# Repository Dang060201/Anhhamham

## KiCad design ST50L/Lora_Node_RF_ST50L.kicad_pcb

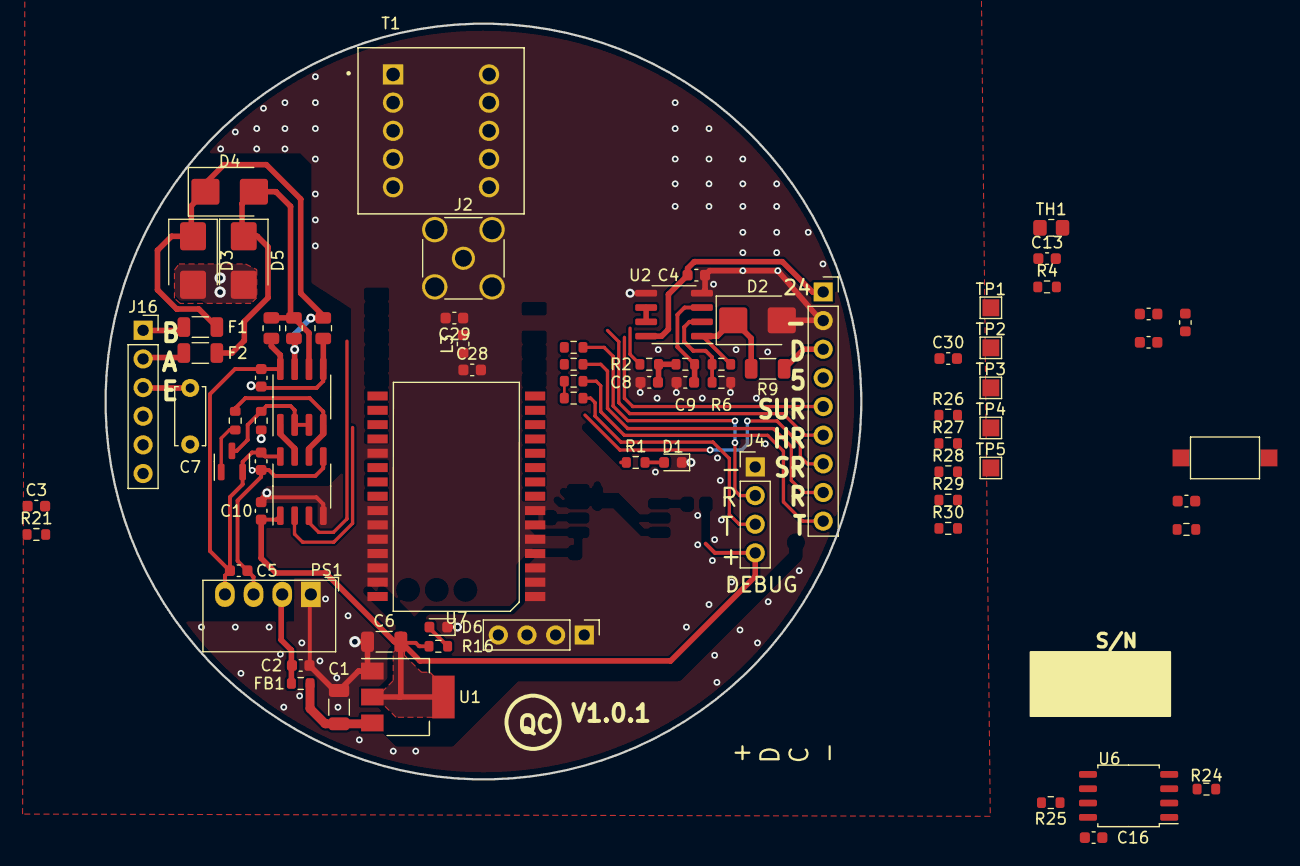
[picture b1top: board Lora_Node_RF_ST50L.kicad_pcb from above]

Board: 2 copper layers, 67.0 x 67.0 mm, 78 parts (0 on the bottom side), 56 nets.

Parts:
C1, C6: 10uF; C_1206_3216Metric
C2, C5: 4.7uF; C_0603_1608Metric
C3, C4, C10, C11, C12, C14, C16: 100nF; C_0603_1608Metric
C7: 4.7nF; C_Disc_D5.0mm_W2.5mm_P5.00mm
C8, C9, C23: 1uF; C_0603_1608Metric
C13: 100n; C_0603_1608Metric
C20: 10uF; C_0603_1608Metric
C28, C29: 7pF; C_0603_1608Metric
C30: 100pF; C_0603_1608Metric
D1, D6: LED; LED_0603_1608Metric
D2: SMBJ12A; D_SMB
D3, D4, D5: SMBJ5.0CA; D_SMB
F1, F2: 0.05A 60V JZ PTC; R_1206_3216Metric
FB1: 100R; R_0603_1608Metric
FB3: FerriteBead; L_0603_1608Metric
J1, J4: Conn_01x04_Pin; PinHeader_1x04_P2.54mm_Vertical
J2: Conn_Coaxial; SMA_Amphenol_132291-12_Vertical
J16: Conn_01x06_Pin; PinSocket_1x06_P2.54mm_Vertical
J17: Conn_01x09_Pin; PinSocket_1x09_P2.54mm_Vertical
L3: 15nH; L_0603_1608Metric
PS1: MEE1S0505SC; Converter_DCDC_Murata_MEE1SxxxxSC_THT
Q1: MMBT3906; SOT-23
R1, R2, R3, R6, R15, R21, R27: 10K; R_0603_1608Metric
R4: 6.8k; R_0603_1608Metric
R5: 33K; R_0603_1608Metric
R7: 6.8K; R_0603_1608Metric
R8: 22K; R_0603_1608Metric
R9: 10R; R_1206_3216Metric
R11, R12, R13: 220R; R_0805_2012Metric
R16: 1K; R_0603_1608Metric
R17, R18, R19, R20: 0R; R_0603_1608Metric
R24, R25: 2.2K; R_0603_1608Metric
R26: 4.7K; R_0603_1608Metric
R28, R29, R30: 22R; R_0603_1608Metric
SW1: SW_Push; SW_SPST_CK_RS282G05A3
T1: EE13; BOBBIN_EE13_6_6
TH1: NTCS0805E3103HLT; R_0805_2012Metric_Pad1.20x1.40mm_HandSolder
TP1, TP4, TP5: digital; TestPoint_Pad_1.5x1.5mm
TP2: 3.3V; TestPoint_Pad_1.5x1.5mm
TP3: GND; TestPoint_Pad_1.5x1.5mm
U1: AMS1117-3.3; SOT-223-3_TabPin2
U2: LM358; SOIC-8_3.9x4.9mm_P1.27mm
U3: CA-IS3722; SOP-8_3.9x4.9mm_P1.27mm
U4: MAX485E; SOIC-8_3.9x4.9mm_P1.27mm
U6: W25Q32JVSS; SOIC-8_5.23x5.23mm_P1.27mm
U7: E77900M22S; E77

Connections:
+3.3V: C6.2, C10.1, C16.1, FB3.2, J1.4, J4.4, R15.1, R16.1, R24.2, R25.2, R26.2, R27.1, TP2.1, U1.2 (VO), U3.1 (VDDA), U6.8 (VCC)
+3.3VP: C14.1, C20.1, FB3.1, U7.28 (VDD)
+5VD: C1.2, FB1.1, J17.4, U1.3 (VI)
+5VP: C5.2, C11.1, C12.1, PS1.4 (+Vout), Q1.2 (E), R13.1, U3.8 (VDDB), U4.8 (VCC)
+24V: C4.1, J17.1, U2.8 (V+)
/A: F2.1, J16.2
/ADC_NTC: C13.1, R4.1, TH1.1, U7.8 (PA1)
/ANT: C28.1, L3.1, U7.14 (ANT)
/A_RS485: D4.2 (A2), D5.1 (A1), F2.2, R12.1, R13.2, U4.6 (A)
/B: F1.1, J16.1
/B_RS485: D3.1 (A1), D4.1 (A1), F1.2, R11.1, R12.2, U4.7 (B)
/DE_RS485: Q1.3 (C), R8.2, U4.2 (~RE), U4.3 (DE)
/DIM10V: J17.3, R9.1
/DS18B20: R26.1, TP1.1, U7.6 (PB8)
/FLASH_CS: U6.1 (~CS), U7.25 (PA15)
/FLASH_HOLD: R25.1, U6.7 (IO3)
/FLASH_MISO: U6.2 (DO(IO1)), U7.2 (PB4)
/FLASH_MOSI: U6.5 (DI(IO0)), U7.3 (PB5)
/FLASH_SCK: U6.6 (CLK), U7.1 (PB3)
/FLASH_WP: R24.1, U6.3 (IO2)
/HLW_RX: J17.8, R19.1
/HLW_TX: J17.9, R20.1
/HRE: R28.2, U7.22 (PB12)
/H_RELAY: J17.6, R28.1
/NRST: C23.1, R15.2, SW1.2, U7.17 (NRST)
/NTC: C3.1, R21.2
/PWM_DAC: R2.1, U7.16 (PA8)
/RUN_LED: R1.1, U7.5 (PB7)
/RX: J4.2, R17.1
/RX_RS485: U3.7 (VI1), U4.1 (RO)
/SRE: R30.2, U7.11 (PA4)
/SURGE: R29.2, U7.23 (PB2)
/SURGE_PULSE: J17.5, R29.1
/SWCLK: J1.3, U7.30 (SWCLK)
/SWDIO: J1.2, U7.29 (SWDIO)
/S_RELAY: J17.7, R30.1
/TX: J4.3, R18.1
/TX_RS485: R7.1, U3.6 (VO2), U4.4 (DI)
/UART1_RX: U3.2 (VO1), U7.21 (PA10)
/UART1_TX: U3.3 (VI2), U7.4 (PB6)
/UART2_RX: R17.2, R19.2, U7.10 (PA3)
/UART2_TX: R18.2, R20.2, U7.9 (PA2)
Earth_Protective: C7.2, J16.3
GND3: C5.1, C7.1, C11.2, C12.2, D3.2 (A2), D5.2 (A2), PS1.3 (-Vout), R8.1, R11.2, U3.5 (GNDB), U4.5 (GND)
GNDPWR: C1.1, C2.1, C3.2, C4.2, C6.1, C8.1, C9.1, C10.2, C13.2, C14.2, C16.2, C20.2, C23.2, C28.2, C29.2, D1.1 (K), D2.2 (A), D6.1 (K), J1.1, J2.2 (Ext), J4.1, J17.2, PS1.1 (-Vin), R6.1, SW1.1, TH1.2, TP3.1, TP5.1, U1.1 (GND), U2.4 (V-), U2.5 (+), U3.4 (GNDA), U6.4 (GND), U7.13 (GND), U7.15 (GND), U7.27 (GND)
unnamed: C8.2, R2.2, R3.1
unnamed: D1.2 (A), R1.2
unnamed: D2.1 (K), R5.2, R9.2, U2.1
unnamed: D6.2 (A), R16.2
unnamed: C29.1, C30.2, J2.1 (In), L3.2
unnamed: C2.2, FB1.2, PS1.2 (+Vin)
unnamed: Q1.1 (B), R7.2
unnamed: R21.1, R27.2, TP4.1
unnamed: C9.2, R3.2, U2.3 (+)
unnamed: R5.1, R6.2, U2.2 (-)
unnamed: U2.6 (-), U2.7

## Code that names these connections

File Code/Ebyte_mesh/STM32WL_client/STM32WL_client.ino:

#define RH_SX126x_MAX_MESSAGE_LEN 50
#include <SPI.h>
#include <RH_STM32WLx.h>
#include <RHMesh.h>
#include <Wire.h>
#include "ClosedCube_HDC1080.h"
#define RUN_LED PA0
#define RELAY PB3
#define num 2
#define CLIENT22_ADDRESS   0
#define SERVER3_ADDRESS  252
ClosedCube_HDC1080 hdc1080;
RH_STM32WLx driver;
RHMesh manager(driver, CLIENT22_ADDRESS);
 
HardwareSerial Serial2(PA3, PA2);
void setup() 
{
  Serial2.begin(115200);
  Wire.setSDA(PB7);
  Wire.setSCL(PB6);
  Wire.begin();
  hdc1080.begin(0x40);

  while (!Serial2) ; // Wait for serial port to be available
  Serial2.println("ClosedCube HDC1080 Arduino Test");

  // Initialize the RF95 module
  if (!driver.init()) {
    Serial2.println("RF95 module initialization failed");
    // while (1);
  }
  else
    Serial2.println("RF95 module initialization sucess");

  if (!manager.init())
    Serial2.println("init failed");
  else
    Serial2.println("init server sucess!");

  // driver.setModemConfig(LoRa_Bw125Cr45Sf128);
  driver.setFrequency(915.0);
  // driver.setSignalBandwidth(434.8);
  if(driver.setTxPower(22) == 1)
  {
    Serial2.println("Set power sucess!");
  }
  else
  {
    Serial2.println("Set power failed!");
  }
  // driver.setCADTimeout(10000);
  // driver.setTxContinuous();
  pinMode(RUN_LED, OUTPUT);
  pinMode(RELAY, OUTPUT);
}

void loop()
{
  Serial2.printf("I'm %d \n", CLIENT22_ADDRESS);
  
  uint8_t buf[RH_SX126x_MAX_MESSAGE_LEN];
  uint8_t len = sizeof(buf);
  uint8_t from;
  uint16_t temp = hdc1080.readTemperature()*100;
  uint16_t humi = hdc1080.readHumidity()*100;

    driver.init();
  // Serial2.println("wait server ping");
  // if(driver.available())
  // {
    // Serial2.print(manager.recvfromAckTimeout(buf, &len,2100, &from));
    // Should be a message for us now   
    if(manager.recvfromAckTimeout(buf, &len, 200, &from))
    {
      digitalWrite(RUN_LED, HIGH);
      Serial2.print("got reply: ");
      for(int i=0;i<num;i++)
      {
        Serial2.println(buf[i]);
      }
      Serial2.print("\nRSSI: ");
      Serial2.println(driver.lastRssi(), DEC);
      uint8_t data[4];
      data[0] = temp >> 8;
      data[1] = temp & 0xff;
      data[2] = humi >> 8;
      data[3] = humi & 0xff;
      if (manager.sendtoWait(data, sizeof(data), from) == RH_ROUTER_ERROR_NONE)
      {
        Serial2.println("sendtoWait success");  
        digitalWrite(RUN_LED, LOW);
      }
      else
      {
        // Serial2.println(manager.sendtoWait(data, sizeof(data), from));
        Serial2.println("sendtoWait failed");
        Serial2.println(from);
        
      }  
    }
    else
    {
      Serial2.println("recv failed");
    }
    if(buf[CLIENT22_ADDRESS]==0){
      digitalWrite(RELAY, LOW);
    }else{
      digitalWrite(RELAY, HIGH);
    }
    

// }
}

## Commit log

2024-04-18 Ánh hết iu Đăng rùi
2024-05-04 anhham
2024-05-06 iu em anh
2024-05-07 Điên
2024-06-28 Data
